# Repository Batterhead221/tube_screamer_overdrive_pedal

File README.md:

# scream_bean (tube screamer based guitar overdrive pedal)

custom overdrive guitar pedal pcb based on the classic tube screamer circuit, made to fit the sound of early 2000s pop/punk (preserve the low frequencies while still adding crunch)

V1 - Will redesign before fab in the future.

Designed & Engineered by Brandon Shelly

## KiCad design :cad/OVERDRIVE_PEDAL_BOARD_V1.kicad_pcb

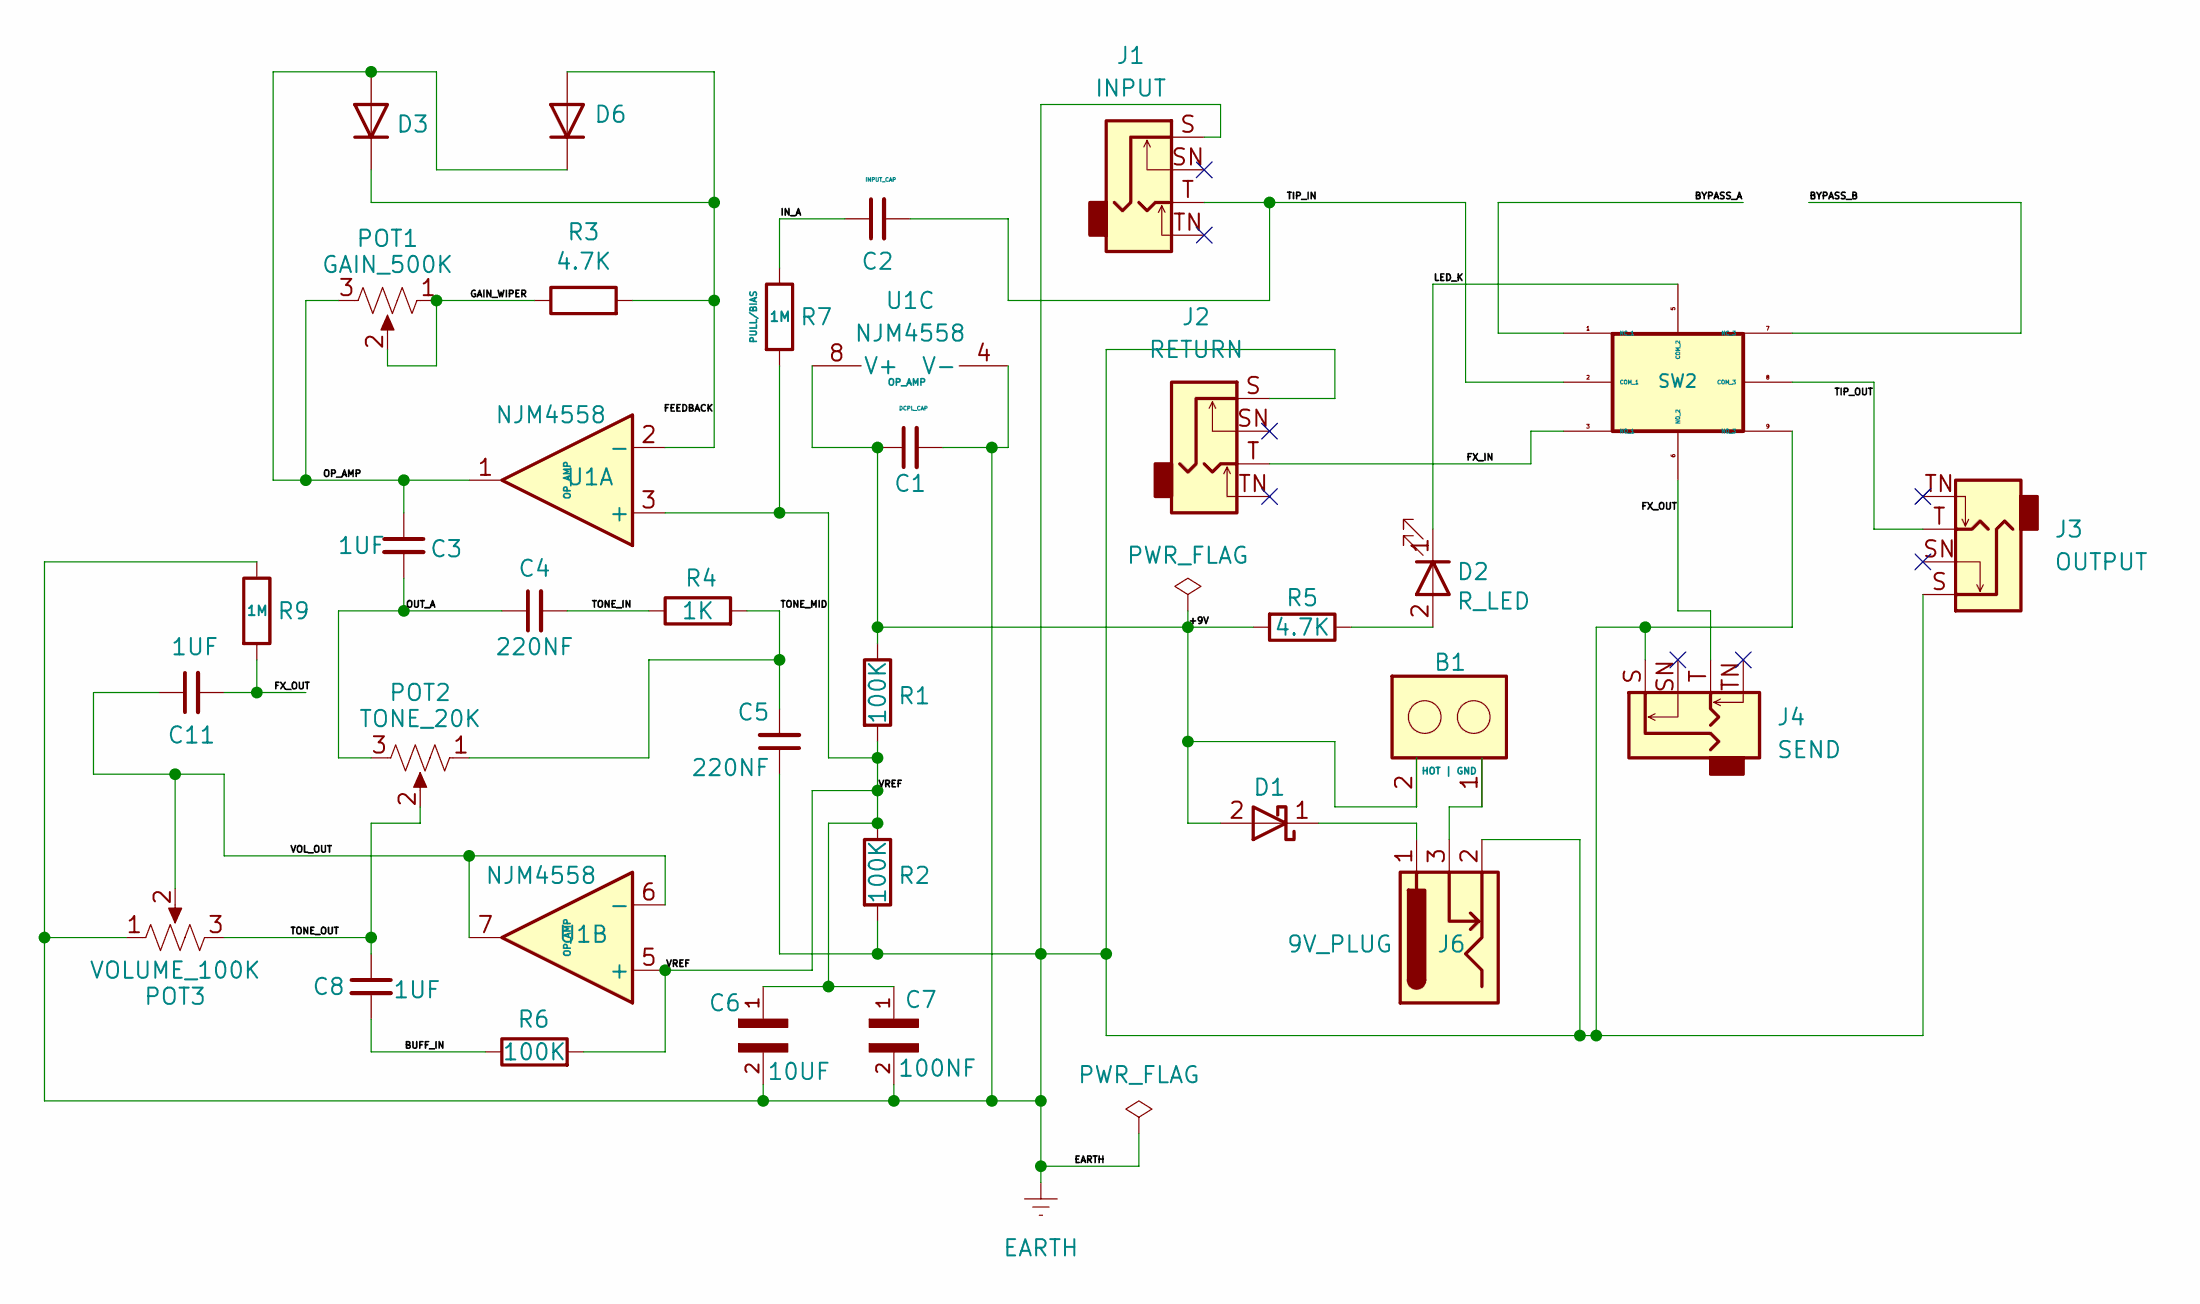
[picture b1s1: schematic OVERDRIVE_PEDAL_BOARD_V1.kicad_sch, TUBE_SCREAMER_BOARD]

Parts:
B1: 1X2_TH_PADS; HOT_GND_THT_PADS
C1: DCPL_CAP; C_0402_1005Metric; Voltage 25V; Tolerance 20%
C2: INPUT_CAP; C_0402_1005Metric; Voltage 25V; Tolerance 20%
C3: 1UF; C_0402_1005Metric; Voltage 6.3V; Tolerance 20%
C4: 220NF; C_0402_1005Metric; Voltage 25V; Tolerance 20%
C5: 220NF; C_0402_1005Metric; Voltage 6.3V; Tolerance 20%
C6: 10UF; CAPC1608X100N; DigiKey_Part_Number 490-18214-1-ND
C7: 100NF; CAPC1005X55N; DigiKey_Part_Number 490-3261-1-ND
C8, C11: 1UF; C_0402_1005Metric; Voltage 25V; Tolerance 20%
D1: 1N5817; D_DO-41_SOD81_P10.16mm_Horizontal
D2: R_LED; LED_0603_1608Metric
D3, D6: 1N4148; D_DO-35_SOD27_P7.62mm_Horizontal
J1: INPUT; Jack_6.35mm_Neutrik_NMJ4HCD2_Horizontal
J2: RETURN; Jack_6.35mm_Neutrik_NMJ4HCD2_Horizontal
J3: OUTPUT; Jack_6.35mm_Neutrik_NMJ4HCD2_Horizontal
J4: SEND; Jack_6.35mm_Neutrik_NMJ4HCD2_Horizontal
J6: 9V_PLUG; Barrel_Jack_PTH
POT1: GAIN_500K; Bourns-PDB18
POT2: TONE_20K; Bourns-PDB18
POT3: VOLUME_100K; Bourns-PDB18
R1, R2, R6: 100K; R_0603_1608Metric
R3, R5: 4.7K; R_0603_1608Metric
R4: 1K; R_0603_1608Metric
R7, R9: 1M; R_0603_1608Metric
SW2: FS57003PLT2B2M2QE; SW_FS57003PLT2B2M2QE
U1: NJM4558; DIP-8_W7.62mm_SMDSocket_SmallPads

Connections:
/+9V: B1.2 (HOT), C1.1, D1.2 (A), R1.1, R5.2, U1.8 (V+)
/BUFF_IN: C8.2, R6.1
/BYPASS_A: SW2.1 (NC_1)
/BYPASS_B: SW2.7 (NC_3)
/FEEDBACK: D3.1 (K), D6.2 (A), R3.2, U1.2 (-)
/FX_IN: J2.T, SW2.3 (NO_1)
/FX_OUT: C11.2, J4.T, R9.2, SW2.6 (NO_2)
/GAIN_WIPER: POT1.1, POT1.2, R3.1
/IN_A: C2.1, R7.1
/LED_K: D2.1 (K), SW2.5 (COM_2)
/OP_AMP: C3.1, D3.2 (A), D6.1 (K), POT1.3, U1.1
/OUT_A: C3.2, C4.1, POT2.3
/TIP_IN: C2.2, J1.T, SW2.2 (COM_1)
/TIP_OUT: J3.T, SW2.8 (COM_3)
/TONE_IN: C4.2, R4.1
/TONE_MID: C5.2, POT2.1, R4.2
/TONE_OUT: C8.1, POT2.2, POT3.3
/VOL_OUT: C11.1, POT3.2, U1.6 (-), U1.7
/VREF: C6.1, C7.1, R1.2, R2.1, R6.2, R7.2, U1.3 (+), U1.5 (+)
EARTH: C1.2, C5.1, C6.2, C7.2, J1.S, J2.S, J3.S, J4.S, J6.2 (GND), POT3.1, R2.2, R9.1, SW2.9 (NO_3), U1.4 (V-)
unnamed: B1.1 (GND), J6.3 (GNDBREAK)
unnamed: D1.1 (K), J6.1 (PWR)
unnamed: D2.2 (A), R5.1

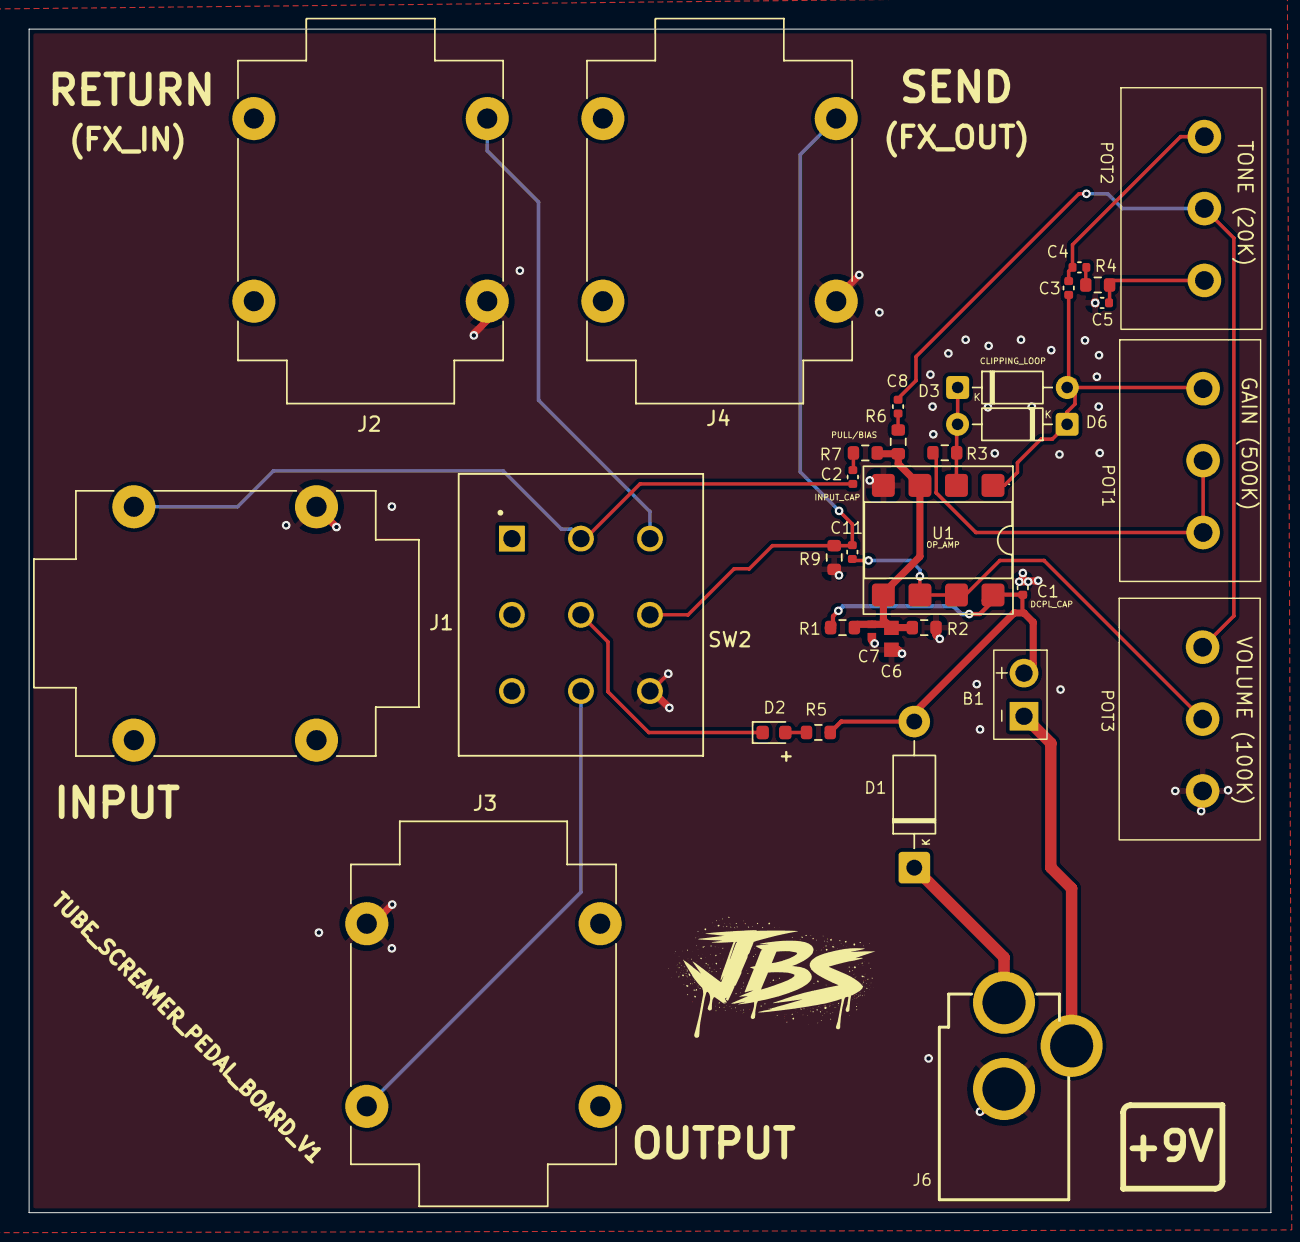
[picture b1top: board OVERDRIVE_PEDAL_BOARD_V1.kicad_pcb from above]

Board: 2 copper layers, 86.3 x 82.3 mm, 32 parts (0 on the bottom side), 21 nets.

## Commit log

2026-04-18 file path restructure
2026-05-03 folder restructure
2026-05-13 Revised repo
2026-05-15 Rename project to scream_bean and update description
    Updated project name and description to reflect changes.
2026-05-15 new rev
